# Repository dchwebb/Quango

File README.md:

# Quango

Quango
--------

Quango is a combined MIDI interface, VCA and envelope for controlling four voice polyphonic Eurorack Modular Oscillators. Polyphonic signal interconnections are made via RJ-45 cables (ie Ethernet cables).

Quango can control two VCOs simultaneously, supplying 1V/Octave pitch information and then shaping the returned audio using 8 ADSR envelopes controlling VCAs for each voice.

The MIDI interface receives both USB and serial MIDI data and also features a calibration mechanism where the pitch CV for each voice is adjusted to correct any tuning errors.

Each of the two channels uses an RJ-45 connector to send CV data on lines 1-4 and receive audio data on lines 5-8. The received audio data is used both for pitch calibration and sent into the ADSR-controlled VCAs.

Both channel voices are mixed and output onto an RJ-45 connection. Additionally each channel's four voices can be separately output on a header on the back of the unit. the gate signal for each voice is also output on an RJ-45 for controlling external envelopes etc.

Additional controls include an octave switch to allow channel B's CV range to be adjusted up or down an octave and a fader to control the overall level of each voice. LEDs show the current level of the VCA of each voice for each channel.

Technical
---------

Quango uses an STM32G473 microcontroller which handles the MIDI interfacing, generates 12-bit DAC signals to control the envelopes, reads the front panel controls from its internal ADCs and controls two external DACs for generating the pitch CV and one envelope (the microcontroller has 7 internal 12 bit DACs so the 8th envelope is supplied from an external 12 bit DAC).

The 1V/Octave Pitch output is generated using an SPI controlled 16-bit 8 channel Analog Devices AD5676 DAC. A Microchip MCP48 12 bit DAC outputs the one envelope generated externally to the microcontroller. Alfa AS3364 quad linear VCAs are used for independent level control of each channel.

A PS508 audio multiplexer switches the 8 audio input channels to a single ADC channel on the microcontroller for pitch detection. Output level LEDs are controlled via PWM from the microcontroller.

Construction is a sandwich of three PCBs with a component board, a controls board and a panel. PCBs designed in Kicad v6.

[Components schematic](https://raw.githubusercontent.com/dchwebb/Quango/master/Hardware/Quango_Components.pdf)

[Controls schematic](https://raw.githubusercontent.com/dchwebb/Quango/master/Hardware/Quango_Controls.pdf)

In addition the the Eurorack +/-12V rails (which have polarity protection and filtering) a 5v rail is supplied using an AMS1117-5.0 LDO. A 3.3v rail is generated with an LM1117-3.3.

Errata
------

Version 1 of the component PCB had the power supply connections to op-amp U14 reversed.

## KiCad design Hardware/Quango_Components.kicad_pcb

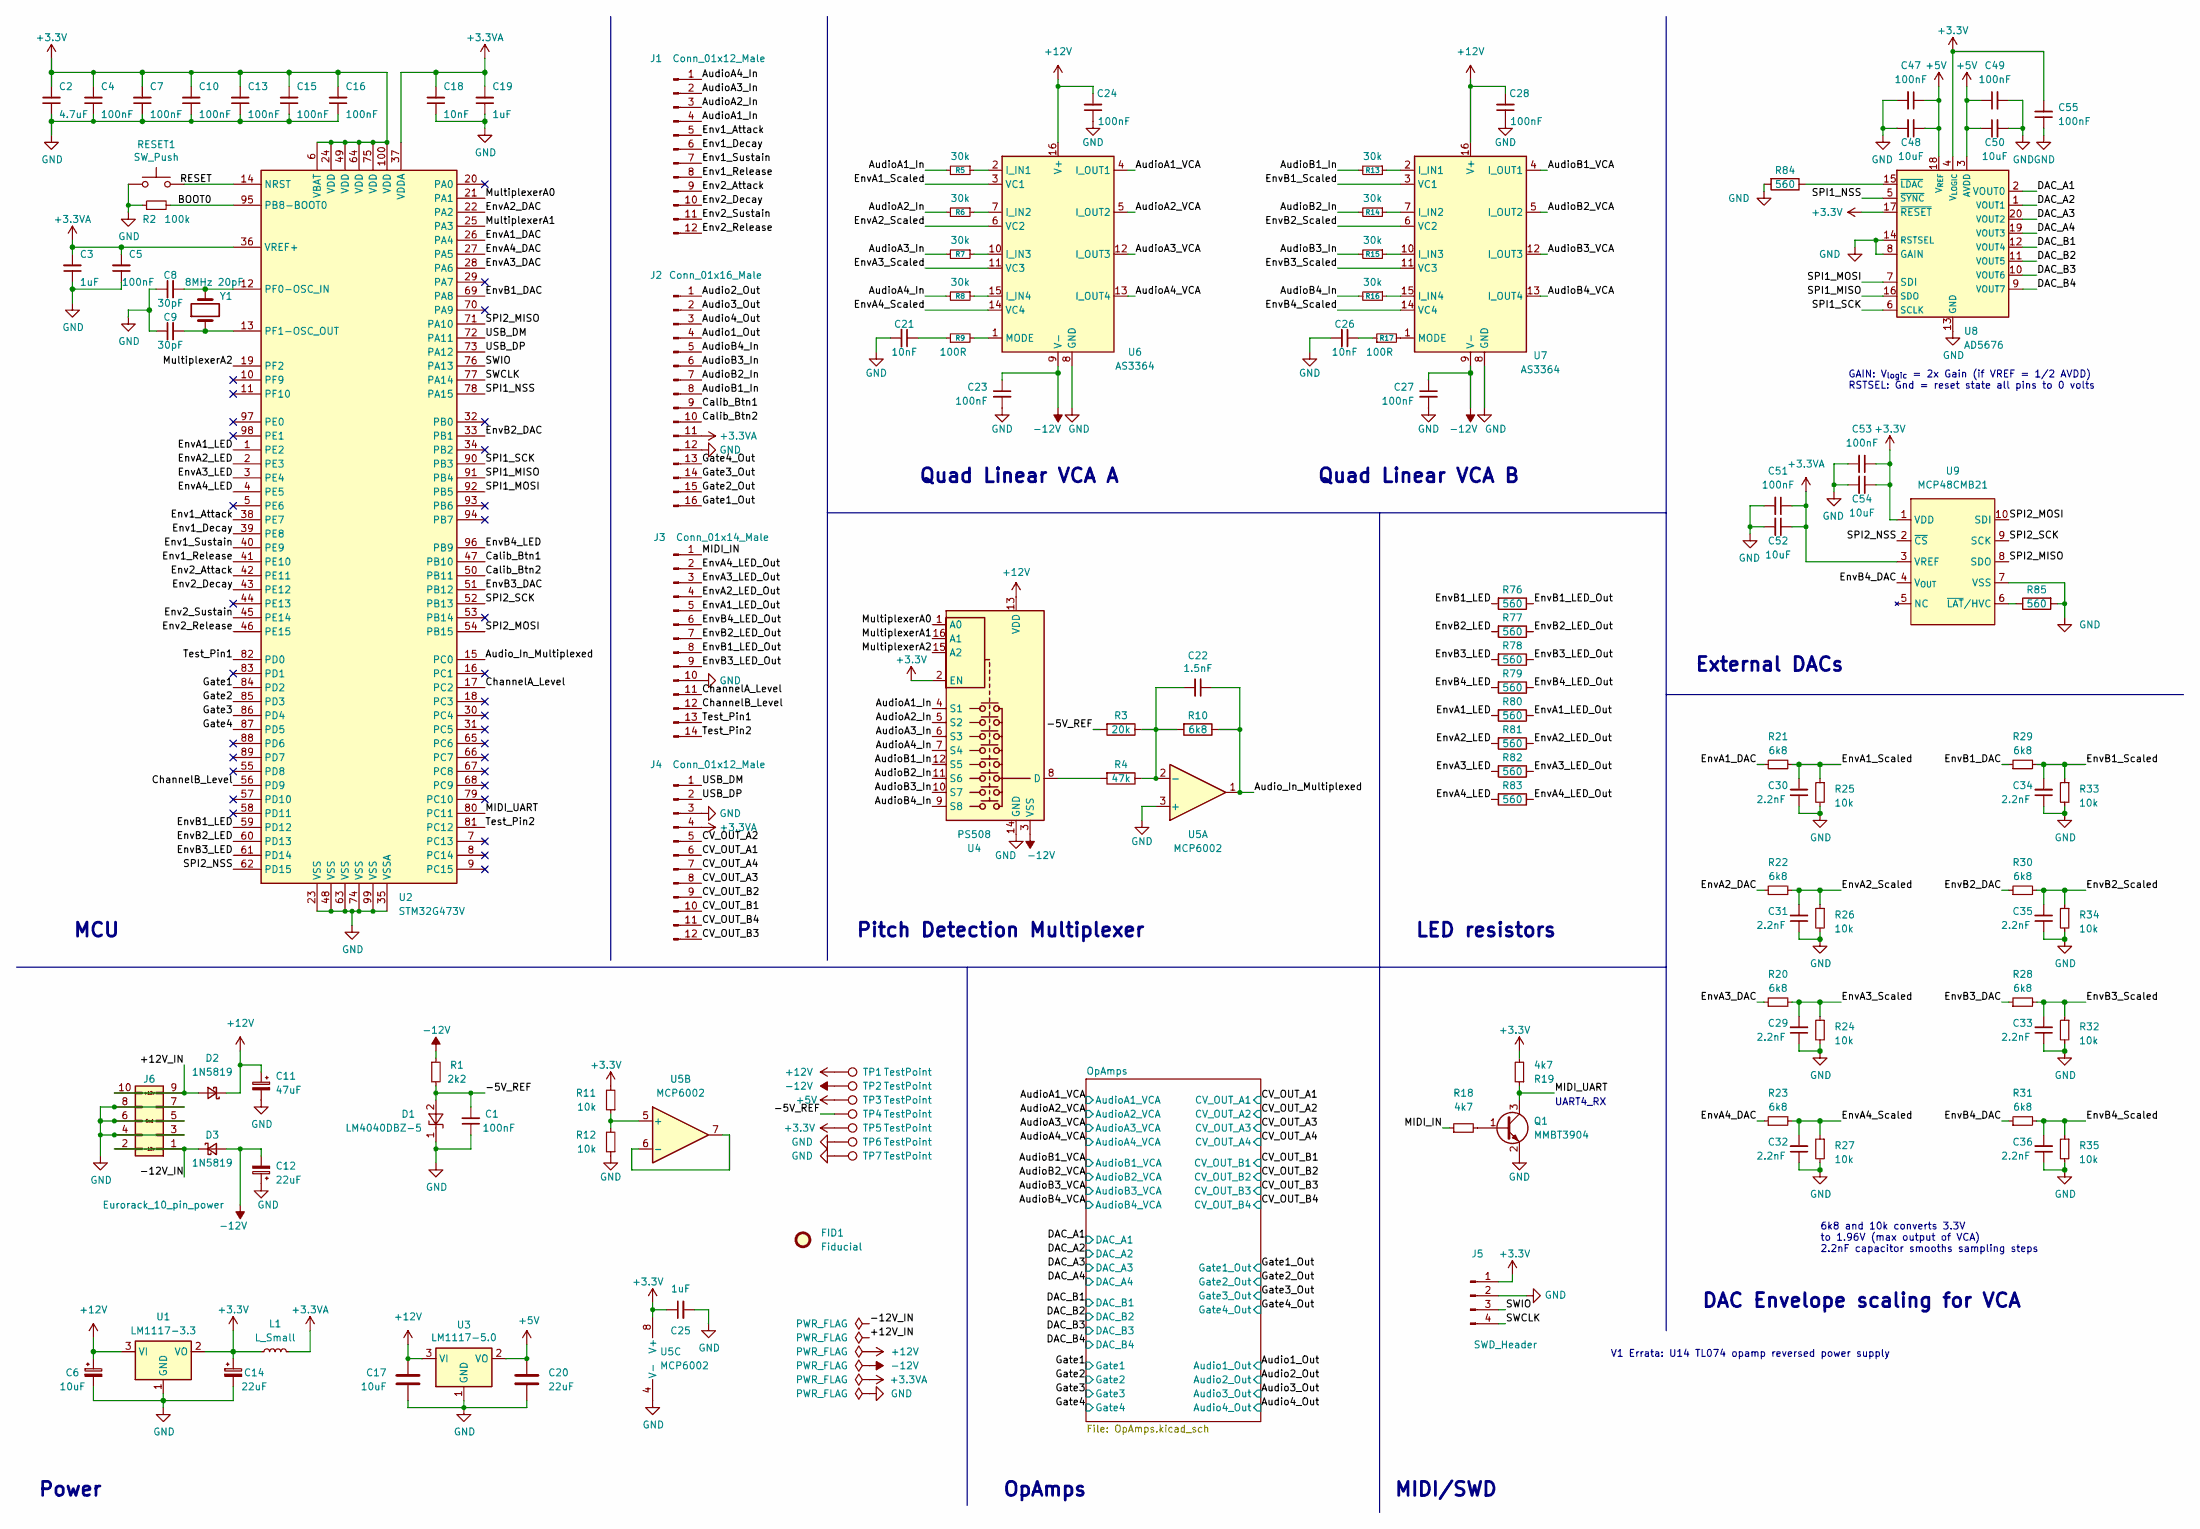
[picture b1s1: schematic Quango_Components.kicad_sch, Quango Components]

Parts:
C1, C4, C5, C7, C10, C13, C15, C16, C23, C24, C27, C28: 100nF; C_0603_1608Metric; Part_Number C14663
C2: 4.7uF; C_0603_1608Metric; Part_Number C19666
C3, C19: 1uF; C_0603_1608Metric; Part_Number C15849
C6, C17: 10uF; C_1206_3216Metric
C8, C9: 30pF; C_0603_1608Metric; Part_Number C22397
C11: 47uF; CP_Elec_4x5.8
C12, C14, C20: 22uF; CP_Elec_4x5.8
C18, C21, C26: 10nF; C_0603_1608Metric; Part_Number C57112
C22: 1.5nF; C_0603_1608Metric; Part_Number C1595
C25: 1uF; C_0603_1608Metric
C29, C30, C31, C32, C33, C34, C35, C36: 2.2nF; C_0603_1608Metric; Part_Number C1604
C47, C49, C51, C53, C55: 100nF; C_0603_1608Metric
C48, C50, C52, C54: 10uF; C_0805_2012Metric
D1: LM4040DBZ-5; SOT-23; Part_Number C156291
D2, D3: 1N5819; D_SOD-123
FID1: Fiducial; 4_Layer_Markers
J1, J4: Conn_01x12_Male; PinHeader_1x12_P2.54mm_Vertical
J2: Conn_01x16_Male; PinHeader_1x16_P2.54mm_Vertical
J3: Conn_01x14_Male; PinHeader_1x14_P2.54mm_Vertical
J5: SWD_Header; SWD_header
J6: Eurorack_10_pin_power; Eurorack_10_pin_header
L1: L_Small; L_0805_2012Metric_Pad1.05x1.20mm_HandSolder; Part_Number C1046
Q1: MMBT3904; SOT-23; Part_Number C20526
R1: 2k2; R_0603_1608Metric; Part_Number C4190
R2: 100k; R_0603_1608Metric; Part_Number C25803
R3: 20k; R_0603_1608Metric; Part_Number C4184
R4: 47k; R_0603_1608Metric; Part_Number C25819
R5, R6, R7, R8, R13, R14, R15, R16: 30k; R_0603_1608Metric; Part_Number C22984
R9, R17: 100R; R_0603_1608Metric; Part_Number C22775
R10, R20, R21, R22, R23, R28, R29, R30, R31: 6k8; R_0603_1608Metric; Part_Number C23212
R11, R12: 10k; R_0603_1608Metric; Part_Number C23162
R18, R19: 4k7; R_0603_1608Metric; Part_Number C23162
R24, R25, R26, R27, R32, R33, R34, R35: 10k; R_0603_1608Metric; Part_Number C25804
R76, R77, R78, R79, R80, R81, R82, R83, R84, R85: 560; R_0603_1608Metric; Part_Number C23212
RESET1: SW_Push; SW_SPST_EVQQ2
TP1, TP2, TP3, TP4, TP5, TP6, TP7: TestPoint; 1mm_Test_Point
U1: LM1117-3.3; SOT-223-3_TabPin2
U2: STM32G473V; LQFP-100_14x14mm_P0.5mm
U3: LM1117-5.0; SOT-223-3_TabPin2
U4: PS508; TSSOP-16_4.4x5mm_P0.65mm
U5: MCP6002; SOIC-8_3.9x4.9mm_P1.27mm
U6, U7: AS3364; SOIC-16_3.9x9.9mm_P1.27mm
U8: AD5676; TSSOP-20_4.4x6.5mm_P0.65mm
U9: MCP48CMB21; MSOP-10_3x3mm_P0.5mm
Y1: 8MHz 20pF; Crystal_SMD_0603-2Pin_6.0x3.5mm; Part_Number C115962

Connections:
+3.3V: C2.2, C4.2, C7.2, C10.2, C13.2, C14.1, C15.2, C16.2, C25.1, C53.1, C54.1, C55.2, J5.1, L1.1, R11.2, R19.2, TP5.1, U1.2 (VO), U2.6 (VBAT), U2.24 (VDD), U2.49 (VDD), U2.64 (VDD), U2.75 (VDD), U2.100 (VDD), U4.2 (EN), U5.8 (V+), U8.4 (V_{LOGIC}), U8.17 (~RESET), U9.1 (VDD)
+3.3VA: C3.2, C5.2, C18.2, C19.2, C51.1, C52.1, J2.11, J4.4, L1.2, U2.36 (VREF+), U2.37 (VDDA), U9.3 (VREF)
+5V: C20.1, C47.1, C48.1, C49.1, C50.1, TP3.1, U3.2 (VO), U8.3 (AVDD), U8.18 (V_{REF})
+12V: C6.1, C11.1, C17.1, C24.2, C28.2, D2.1 (K), TP1.1, U1.3 (VI), U3.3 (VI), U4.13 (VDD), U6.16 (V+), U7.16 (V+); also elsewhere on the board
-12V: C12.2, C23.1, C27.1, D3.2 (A), R1.1, TP2.1, U4.3 (VSS), U6.9 (V-), U7.9 (V-); also elsewhere on the board
/+12V_IN: D2.2 (A), J6.9, J6.10
/-5V_REF: C1.2, D1.2 (A), R1.2, R3.2, TP4.1
/-12V_IN: D3.1 (K), J6.1, J6.2
/Audio1_Out: J2.4; also elsewhere on the board
/Audio2_Out: J2.1; also elsewhere on the board
/Audio3_Out: J2.2; also elsewhere on the board
/Audio4_Out: J2.3; also elsewhere on the board
/AudioA1_In: J1.4, R5.2, U4.4 (S1)
/AudioA1_VCA: U6.4 (I_OUT1); also elsewhere on the board
/AudioA2_In: J1.3, R6.2, U4.5 (S2)
/AudioA2_VCA: U6.5 (I_OUT2); also elsewhere on the board
/AudioA3_In: J1.2, R7.2, U4.6 (S3)
/AudioA3_VCA: U6.12 (I_OUT3); also elsewhere on the board
/AudioA4_In: J1.1, R8.2, U4.7 (S4)
/AudioA4_VCA: U6.13 (I_OUT4); also elsewhere on the board
/AudioB1_In: J2.8, R13.2, U4.12 (S5)
/AudioB1_VCA: U7.4 (I_OUT1); also elsewhere on the board
/AudioB2_In: J2.7, R14.2, U4.11 (S6)
/AudioB2_VCA: U7.5 (I_OUT2); also elsewhere on the board
/AudioB3_In: J2.6, R15.2, U4.10 (S7)
/AudioB3_VCA: U7.12 (I_OUT3); also elsewhere on the board
/AudioB4_In: J2.5, R16.2, U4.9 (S8)
/AudioB4_VCA: U7.13 (I_OUT4); also elsewhere on the board
/Audio_In_Multiplexed: C22.1, R10.1, U2.15 (PC0), U5.1
/BOOT0: R2.2, U2.95 (PB8-BOOT0)
/CV_OUT_A1: J4.6; also elsewhere on the board
/CV_OUT_A2: J4.5; also elsewhere on the board
/CV_OUT_A3: J4.8; also elsewhere on the board
/CV_OUT_A4: J4.7; also elsewhere on the board
/CV_OUT_B1: J4.10; also elsewhere on the board
/CV_OUT_B2: J4.9; also elsewhere on the board
/CV_OUT_B3: J4.12; also elsewhere on the board
/CV_OUT_B4: J4.11; also elsewhere on the board
/Calib_Btn1: J2.9, U2.47 (PB10)
/Calib_Btn2: J2.10, U2.50 (PB11)
/ChannelA_Level: J3.11, U2.17 (PC2)
/ChannelB_Level: J3.12, U2.56 (PD9)
/DAC_A1: U8.2 (VOUT0); also elsewhere on the board
/DAC_A2: U8.1 (VOUT1); also elsewhere on the board
/DAC_A3: U8.20 (VOUT2); also elsewhere on the board
/DAC_A4: U8.19 (VOUT3); also elsewhere on the board
/DAC_B1: U8.12 (VOUT4); also elsewhere on the board
/DAC_B2: U8.11 (VOUT5); also elsewhere on the board
/DAC_B3: U8.10 (VOUT6); also elsewhere on the board
/DAC_B4: U8.9 (VOUT7); also elsewhere on the board
/Env1_Attack: J1.5, U2.38 (PE7)
/Env1_Decay: J1.6, U2.39 (PE8)
/Env1_Release: J1.8, U2.41 (PE10)
/Env1_Sustain: J1.7, U2.40 (PE9)
/Env2_Attack: J1.9, U2.42 (PE11)
/Env2_Decay: J1.10, U2.43 (PE12)
/Env2_Release: J1.12, U2.46 (PE15)
/Env2_Sustain: J1.11, U2.45 (PE14)
/EnvA1_DAC: R21.1, U2.26 (PA4)
/EnvA1_LED: R80.2, U2.1 (PE2)
/EnvA1_LED_Out: J3.5, R80.1
/EnvA1_Scaled: C30.2, R21.2, R25.1, U6.3 (VC1)
/EnvA2_DAC: R22.1, U2.22 (PA2)
/EnvA2_LED: R81.2, U2.2 (PE3)
/EnvA2_LED_Out: J3.4, R81.1
/EnvA2_Scaled: C31.2, R22.2, R26.1, U6.6 (VC2)
/EnvA3_DAC: R20.1, U2.28 (PA6)
/EnvA3_LED: R82.2, U2.3 (PE4)
/EnvA3_LED_Out: J3.3, R82.1
/EnvA3_Scaled: C29.2, R20.2, R24.1, U6.11 (VC3)
/EnvA4_DAC: R23.1, U2.27 (PA5)
/EnvA4_LED: R83.2, U2.4 (PE5)
/EnvA4_LED_Out: J3.2, R83.1
/EnvA4_Scaled: C32.2, R23.2, R27.1, U6.14 (VC4)
/EnvB1_DAC: R29.1, U2.69 (PA8)
/EnvB1_LED: R76.2, U2.59 (PD12)
/EnvB1_LED_Out: J3.8, R76.1
/EnvB1_Scaled: C34.2, R29.2, R33.1, U7.3 (VC1)
/EnvB2_DAC: R30.1, U2.33 (PB1)
/EnvB2_LED: R77.2, U2.60 (PD13)
/EnvB2_LED_Out: J3.7, R77.1
/EnvB2_Scaled: C35.2, R30.2, R34.1, U7.6 (VC2)
/EnvB3_DAC: R28.1, U2.51 (PB12)
/EnvB3_LED: R78.2, U2.61 (PD14)
/EnvB3_LED_Out: J3.9, R78.1
/EnvB3_Scaled: C33.2, R28.2, R32.1, U7.11 (VC3)
/EnvB4_DAC: R31.1, U9.4 (V_{OUT})
/EnvB4_LED: R79.2, U2.96 (PB9)
/EnvB4_LED_Out: J3.6, R79.1
/EnvB4_Scaled: C36.2, R31.2, R35.1, U7.14 (VC4)
/Gate1: U2.84 (PD2); also elsewhere on the board
/Gate1_Out: J2.16; also elsewhere on the board
/Gate2: U2.85 (PD3); also elsewhere on the board
/Gate2_Out: J2.15; also elsewhere on the board
/Gate3: U2.86 (PD4); also elsewhere on the board
/Gate3_Out: J2.14; also elsewhere on the board
/Gate4: U2.87 (PD5); also elsewhere on the board
/Gate4_Out: J2.13; also elsewhere on the board
/MIDI_IN: J3.1, R18.1
/MIDI_UART: Q1.3 (C), R19.1, U2.80 (PC11)
/MultiplexerA0: U2.21 (PA1), U4.1 (A0)
/MultiplexerA1: U2.25 (PA3), U4.16 (A1)
/MultiplexerA2: U2.19 (PF2), U4.15 (A2)
/RESET: RESET1.1, U2.14 (NRST)
/SPI1_MISO: U2.91 (PB4), U8.16 (SDO)
/SPI1_MOSI: U2.92 (PB5), U8.7 (SDI)
/SPI1_NSS: U2.78 (PA15), U8.5 (~SYNC)
/SPI1_SCK: U2.90 (PB3), U8.6 (SCLK)
/SPI2_MISO: U2.71 (PA10), U9.8 (SDO)
/SPI2_MOSI: U2.54 (PB15), U9.10 (SDI)
/SPI2_NSS: U2.62 (PD15), U9.2 (~CS)
/SPI2_SCK: U2.52 (PB13), U9.9 (SCK)
/SWCLK: J5.4, U2.77 (PA14)
/SWIO: J5.3, U2.76 (PA13)
/Test_Pin1: J3.13, U2.82 (PD0)
/Test_Pin2: J3.14, U2.81 (PC12)
/USB_DM: J4.1, U2.72 (PA11)
/USB_DP: J4.2, U2.73 (PA12)
GND: C1.1, C2.1, C3.1, C4.1, C5.1, C6.2, C7.1, C8.1, C9.1, C10.1, C11.2, C12.1, C13.1, C14.2, C15.1, C16.1, C17.2, C18.1, C19.1, C20.2, C21.2, C23.2, C24.1, C25.2, C26.2, C27.2, C28.1, C29.1, C30.1, C31.1, C32.1, C33.1, C34.1, C35.1, C36.1, C47.2, C48.2, C49.2, C50.2, C51.2, C52.2, C53.2, C54.2, C55.1, D1.1 (K), J2.12, J3.10, J4.3, J5.2, J6.3, J6.4, J6.5, J6.6, J6.7, J6.8, Q1.2 (E), R2.1, R12.1, R24.2, R25.2, R26.2, R27.2, R32.2, R33.2, R34.2, R35.2, R84.2, R85.2, RESET1.2, TP6.1, TP7.1, U1.1 (GND), U2.23 (VSS), U2.35 (VSSA), U2.48 (VSS), U2.63 (VSS), U2.74 (VSS), U2.99 (VSS), U3.1 (GND), U4.14 (GND), U5.3 (+), U5.4 (V-), U6.8 (GND), U7.8 (GND), U8.8 (GAIN), U8.13 (GND), U8.14 (RSTSEL), U9.7 (VSS); also elsewhere on the board
unnamed: C21.1, R9.1
unnamed: C26.1, R17.1
unnamed: Q1.1 (B), R18.2
unnamed: C8.2, U2.12 (PF0-OSC_IN), Y1.2
unnamed: C9.2, U2.13 (PF1-OSC_OUT), Y1.1
unnamed: R4.2, U4.8 (D)
unnamed: C22.2, R3.1, R4.1, R10.2, U5.2 (-)
unnamed: R11.1, R12.2, U5.5 (+)
unnamed: U5.6 (-), U5.7
unnamed: R5.1, U6.2 (I_IN1)
unnamed: R6.1, U6.7 (I_IN2)
unnamed: R7.1, U6.10 (I_IN3)
unnamed: R8.1, U6.15 (I_IN4)
unnamed: R9.2, U6.1 (MODE)
unnamed: R13.1, U7.2 (I_IN1)
unnamed: R14.1, U7.7 (I_IN2)
unnamed: R15.1, U7.10 (I_IN3)
unnamed: R16.1, U7.15 (I_IN4)
unnamed: R17.2, U7.1 (MODE)
unnamed: R84.1, U8.15 (~LDAC)
unnamed: R85.1, U9.6 (~LAT/HVC)

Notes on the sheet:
Pitch Detection Multiplexer
DAC Envelope scaling for VCA
Power
V1 Errata: U14 TL074 opamp reversed power supply
MCU
UART4_RX
GAIN: V_{logic} = 2x Gain (if VREF = 1/2 AVDD) RSTSEL: Gnd = reset state all pins to 0 volts
6k8 and 10k converts 3.3V to 1.96V (max output of VCA) 2.2nF capacitor smooths sampling steps
LED resistors
OpAmps
External DACs
Quad Linear VCA B
MIDI/SWD
Quad Linear VCA A

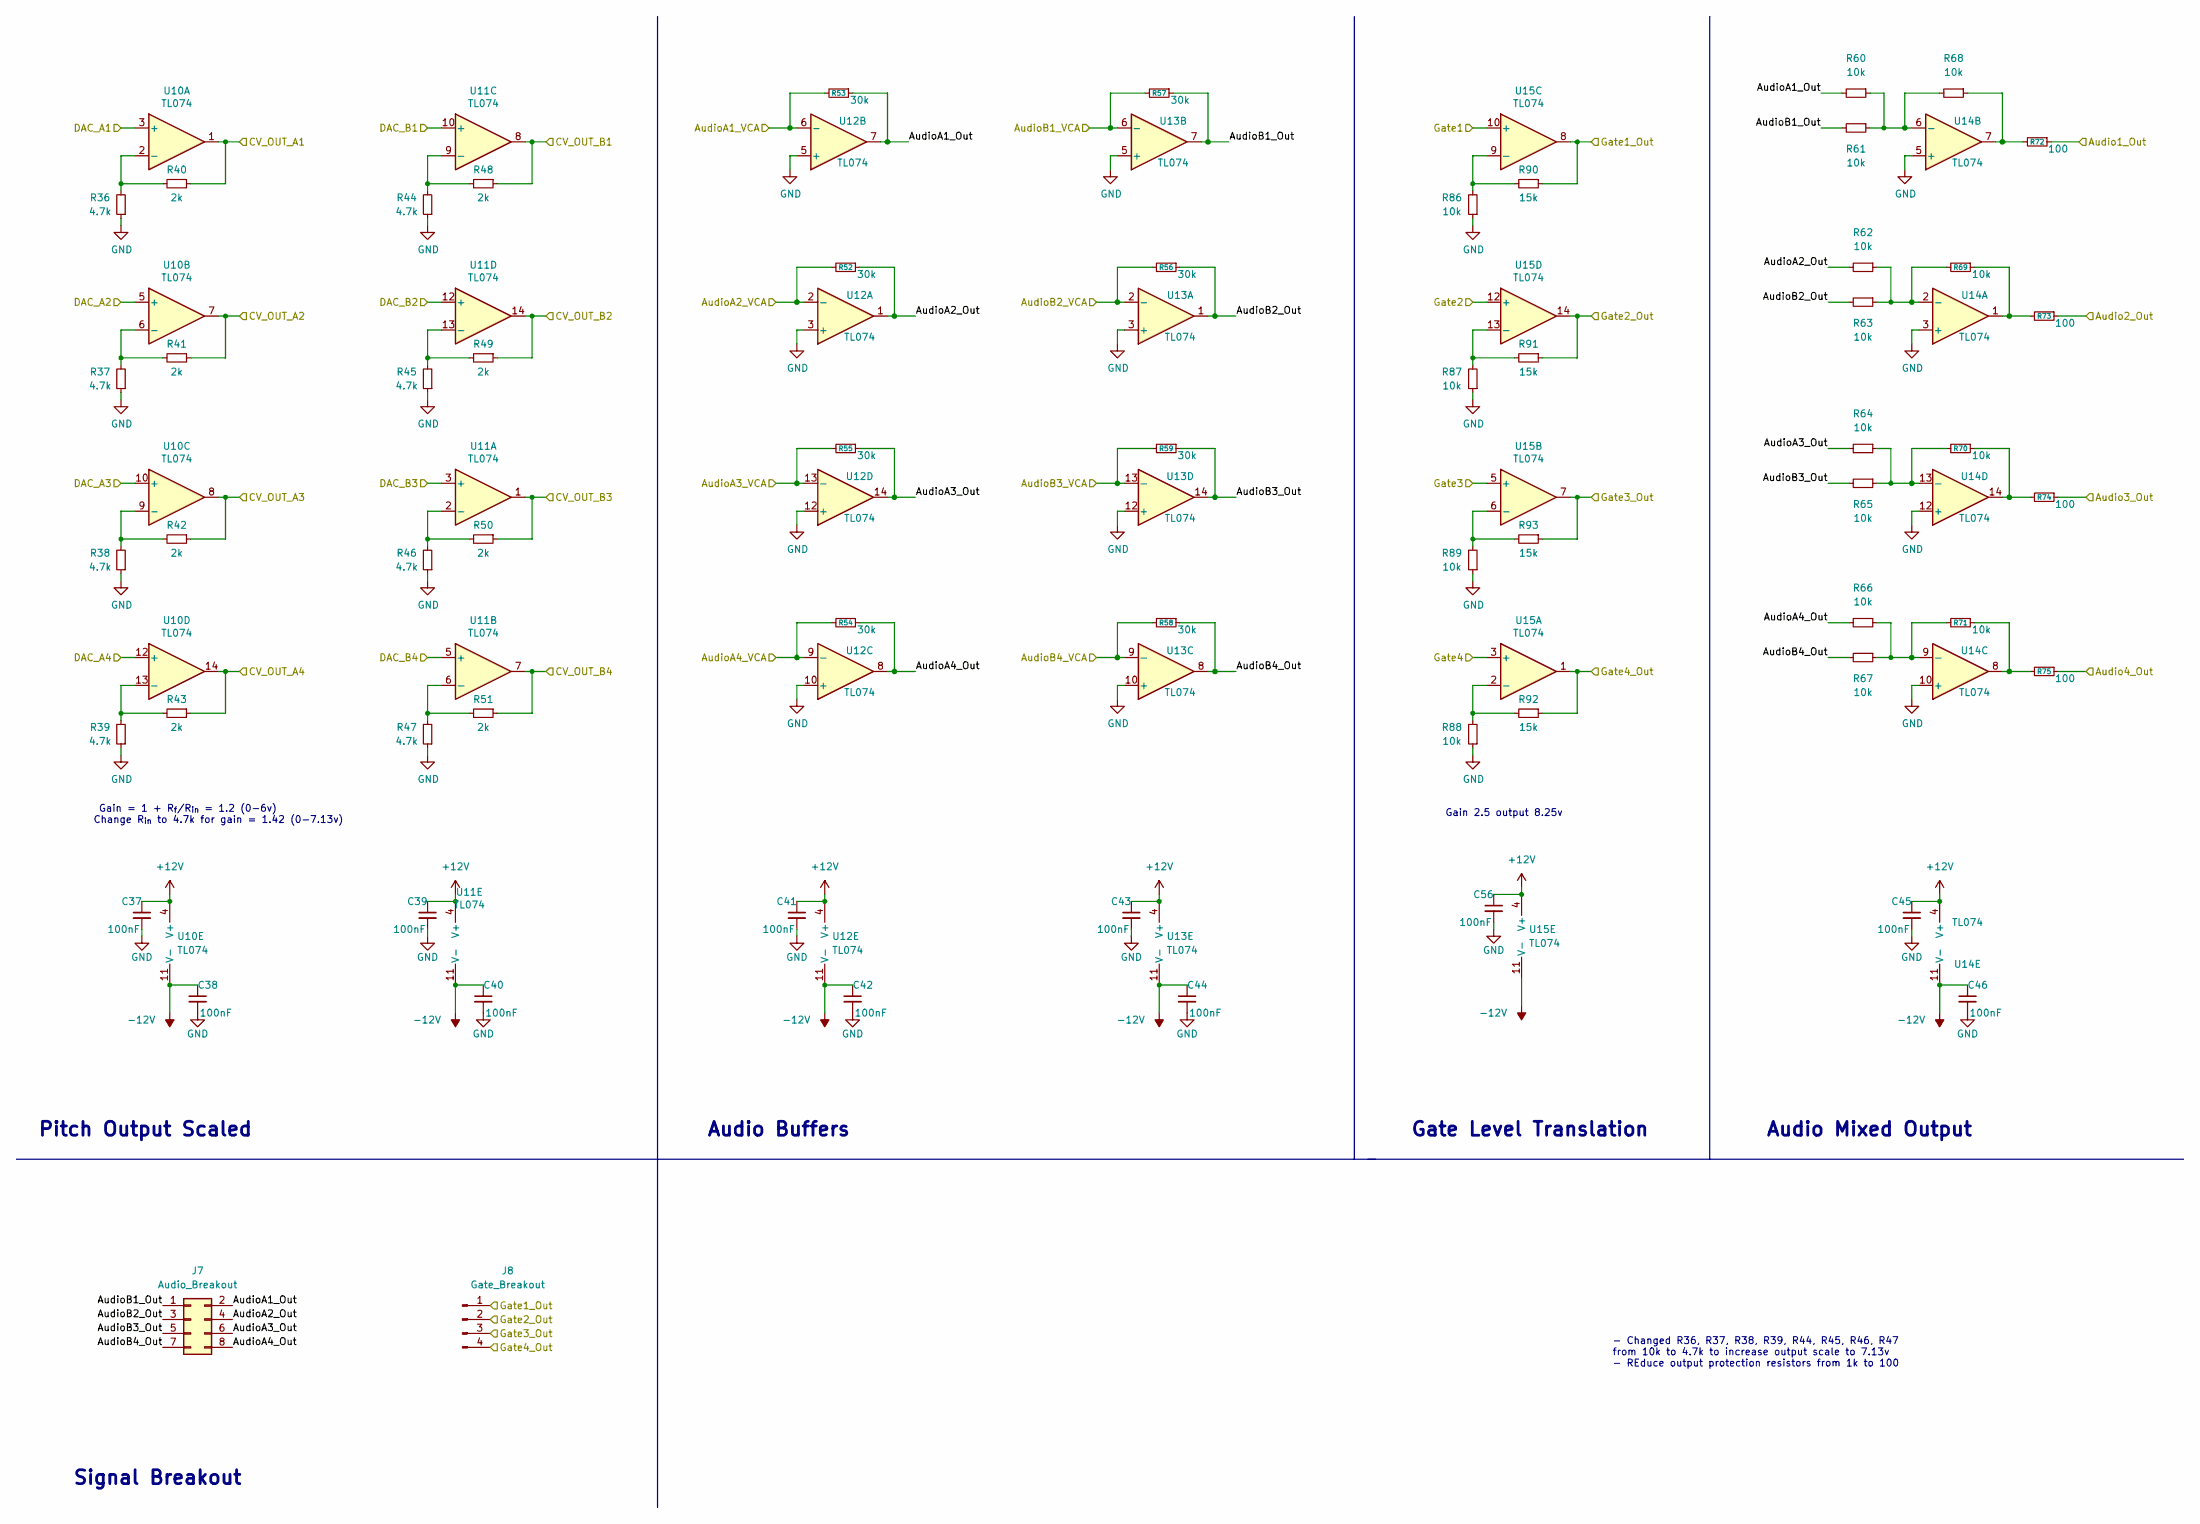
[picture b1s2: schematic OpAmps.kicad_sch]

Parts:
C37, C38, C39, C40, C41, C42, C43, C44, C45, C46, C56: 100nF; C_0603_1608Metric; Part_Number C23630
J7: Audio_Breakout; PinHeader_2x04_P2.54mm_Vertical
J8: Gate_Breakout; PinHeader_1x04_P2.54mm_Vertical
R36, R37, R38, R39, R44, R45, R46, R47: 4.7k; R_0603_1608Metric
R40, R41, R42, R43, R48, R49, R50, R51: 2k; R_0603_1608Metric
R52, R53, R54, R55, R56, R57, R58, R59: 30k; R_0603_1608Metric; Part_Number C22984
R60, R61, R62, R63, R64, R65, R66, R67, R68, R69, R70, R71: 10k; R_0603_1608Metric; Part_Number C22984
R72, R73, R74, R75: 100; R_0603_1608Metric; Part_Number C21190
R86, R87, R88, R89: 10k; R_0603_1608Metric
R90, R91, R92, R93: 15k; R_0603_1608Metric
U10, U11, U12, U13, U14, U15: TL074; TSSOP-14_4.4x5mm_P0.65mm

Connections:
+12V: C37.1, C39.1, C41.1, C43.1, C45.1, C56.1, U10.4 (V+), U11.4 (V+), U12.4 (V+), U13.4 (V+), U14.4 (V+), U15.4 (V+); also elsewhere on the board
-12V: C38.1, C40.1, C42.1, C44.1, C46.1, U10.11 (V-), U11.11 (V-), U12.11 (V-), U13.11 (V-), U14.11 (V-), U15.11 (V-); also elsewhere on the board
/Audio1_Out: R72.1; also elsewhere on the board
/Audio2_Out: R73.1; also elsewhere on the board
/Audio3_Out: R74.1; also elsewhere on the board
/Audio4_Out: R75.1; also elsewhere on the board
/AudioA1_VCA: R53.2, U12.6 (-); also elsewhere on the board
/AudioA2_VCA: R52.2, U12.2 (-); also elsewhere on the board
/AudioA3_VCA: R55.2, U12.13 (-); also elsewhere on the board
/AudioA4_VCA: R54.2, U12.9 (-); also elsewhere on the board
/AudioB1_VCA: R57.2, U13.6 (-); also elsewhere on the board
/AudioB2_VCA: R56.2, U13.2 (-); also elsewhere on the board
/AudioB3_VCA: R59.2, U13.13 (-); also elsewhere on the board
/AudioB4_VCA: R58.2, U13.9 (-); also elsewhere on the board
/CV_OUT_A1: R40.1, U10.1; also elsewhere on the board
/CV_OUT_A2: R41.1, U10.7; also elsewhere on the board
/CV_OUT_A3: R42.1, U10.8; also elsewhere on the board
/CV_OUT_A4: R43.1, U10.14; also elsewhere on the board
/CV_OUT_B1: R48.1, U11.8; also elsewhere on the board
/CV_OUT_B2: R49.1, U11.14; also elsewhere on the board
/CV_OUT_B3: R50.1, U11.1; also elsewhere on the board
/CV_OUT_B4: R51.1, U11.7; also elsewhere on the board
/DAC_A1: U10.3 (+); also elsewhere on the board
/DAC_A2: U10.5 (+); also elsewhere on the board
/DAC_A3: U10.10 (+); also elsewhere on the board
/DAC_A4: U10.12 (+); also elsewhere on the board
/DAC_B1: U11.10 (+); also elsewhere on the board
/DAC_B2: U11.12 (+); also elsewhere on the board
/DAC_B3: U11.3 (+); also elsewhere on the board
/DAC_B4: U11.5 (+); also elsewhere on the board
/Gate1: U15.10 (+); also elsewhere on the board
/Gate1_Out: J8.1, R90.1, U15.8; also elsewhere on the board
/Gate2: U15.12 (+); also elsewhere on the board
/Gate2_Out: J8.2, R91.1, U15.14; also elsewhere on the board
/Gate3: U15.5 (+); also elsewhere on the board
/Gate3_Out: J8.3, R93.1, U15.7; also elsewhere on the board
/Gate4: U15.3 (+); also elsewhere on the board
/Gate4_Out: J8.4, R92.1, U15.1; also elsewhere on the board
/OpAmps/AudioA1_Out: J7.2, R53.1, R60.2, U12.7
/OpAmps/AudioA2_Out: J7.4, R52.1, R62.2, U12.1
/OpAmps/AudioA3_Out: J7.6, R55.1, R64.2, U12.14
/OpAmps/AudioA4_Out: J7.8, R54.1, R66.2, U12.8
/OpAmps/AudioB1_Out: J7.1, R57.1, R61.2, U13.7
/OpAmps/AudioB2_Out: J7.3, R56.1, R63.2, U13.1
/OpAmps/AudioB3_Out: J7.5, R59.1, R65.2, U13.14
/OpAmps/AudioB4_Out: J7.7, R58.1, R67.2, U13.8
GND: C37.2, C38.2, C39.2, C40.2, C41.2, C42.2, C43.2, C44.2, C45.2, C46.2, C56.2, R36.1, R37.1, R38.1, R39.1, R44.1, R45.1, R46.1, R47.1, R86.1, R87.1, R88.1, R89.1, U12.3 (+), U12.5 (+), U12.10 (+), U12.12 (+), U13.3 (+), U13.5 (+), U13.10 (+), U13.12 (+), U14.3 (+), U14.5 (+), U14.10 (+), U14.12 (+); also elsewhere on the board
unnamed: R68.1, R72.2, U14.7
unnamed: R69.1, R73.2, U14.1
unnamed: R70.1, R74.2, U14.14
unnamed: R71.1, R75.2, U14.8
unnamed: R36.2, R40.2, U10.2 (-)
unnamed: R37.2, R41.2, U10.6 (-)
unnamed: R38.2, R42.2, U10.9 (-)
unnamed: R39.2, R43.2, U10.13 (-)
unnamed: R46.2, R50.2, U11.2 (-)
unnamed: R47.2, R51.2, U11.6 (-)
unnamed: R44.2, R48.2, U11.9 (-)
unnamed: R45.2, R49.2, U11.13 (-)
unnamed: R62.1, R63.1, R69.2, U14.2 (-)
unnamed: R60.1, R61.1, R68.2, U14.6 (-)
unnamed: R66.1, R67.1, R71.2, U14.9 (-)
unnamed: R64.1, R65.1, R70.2, U14.13 (-)
unnamed: R88.2, R92.2, U15.2 (-)
unnamed: R89.2, R93.2, U15.6 (-)
unnamed: R86.2, R90.2, U15.9 (-)
unnamed: R87.2, R91.2, U15.13 (-)

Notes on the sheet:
Signal Breakout
Gate Level Translation
Audio Buffers
Pitch Output Scaled
Audio Mixed Output
Gain 2.5 output 8.25v
Gain = 1 + R_{f}/R_{in} = 1.2 (0-6v) Change R_{in} to 4.7k for gain = 1.42 (0-7.13v)
- Changed R36, R37, R38, R39, R44, R45, R46, R47 from 10k to 4.7k to increase output scale to 7.13v - REduce output protection resistors from 1k to 100

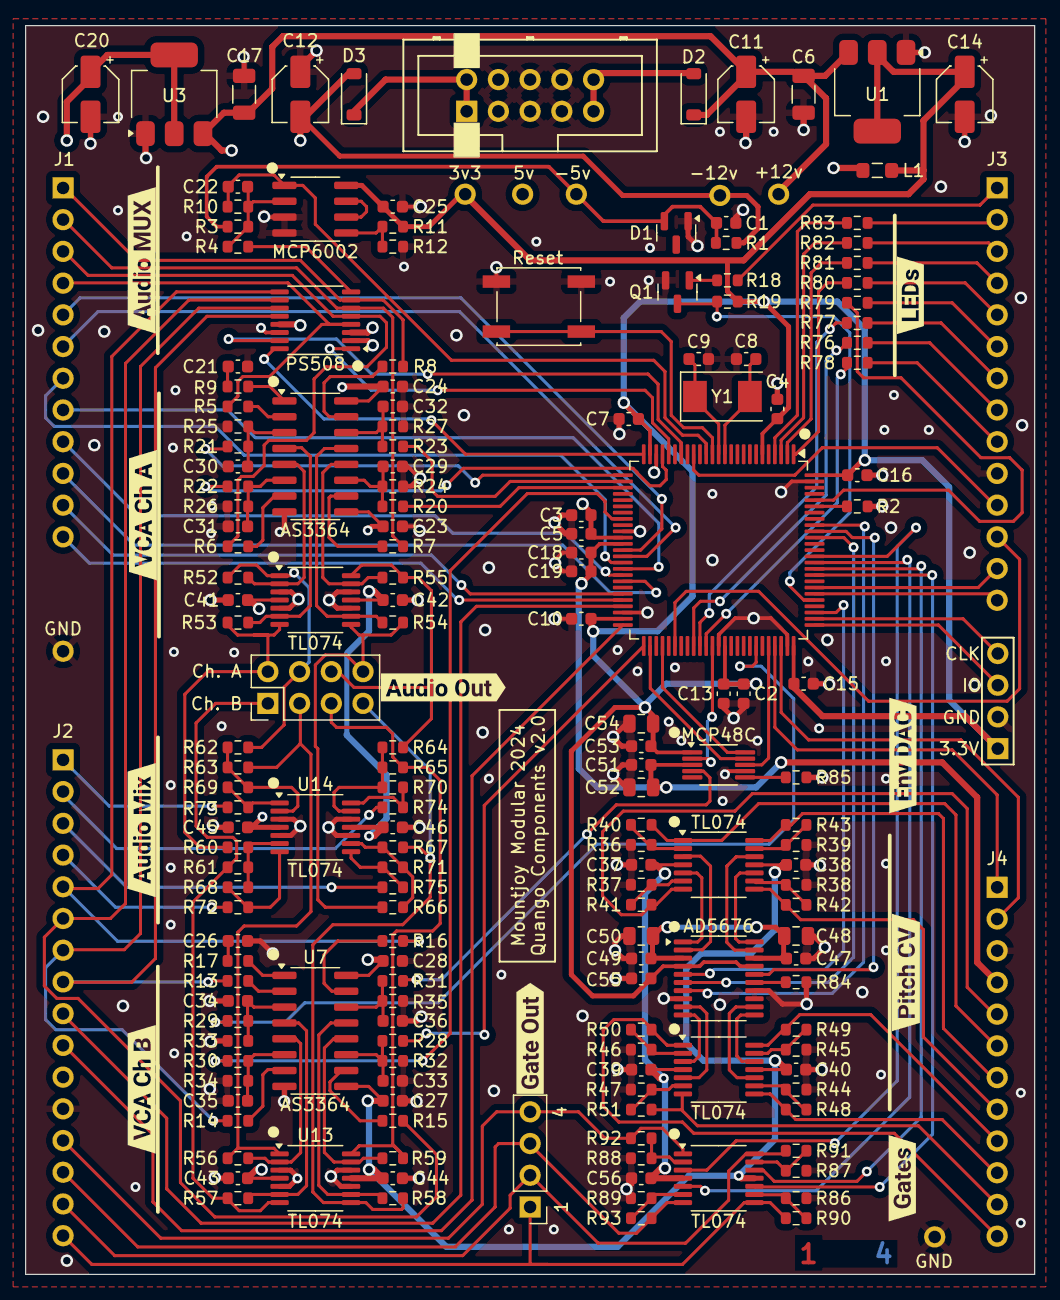
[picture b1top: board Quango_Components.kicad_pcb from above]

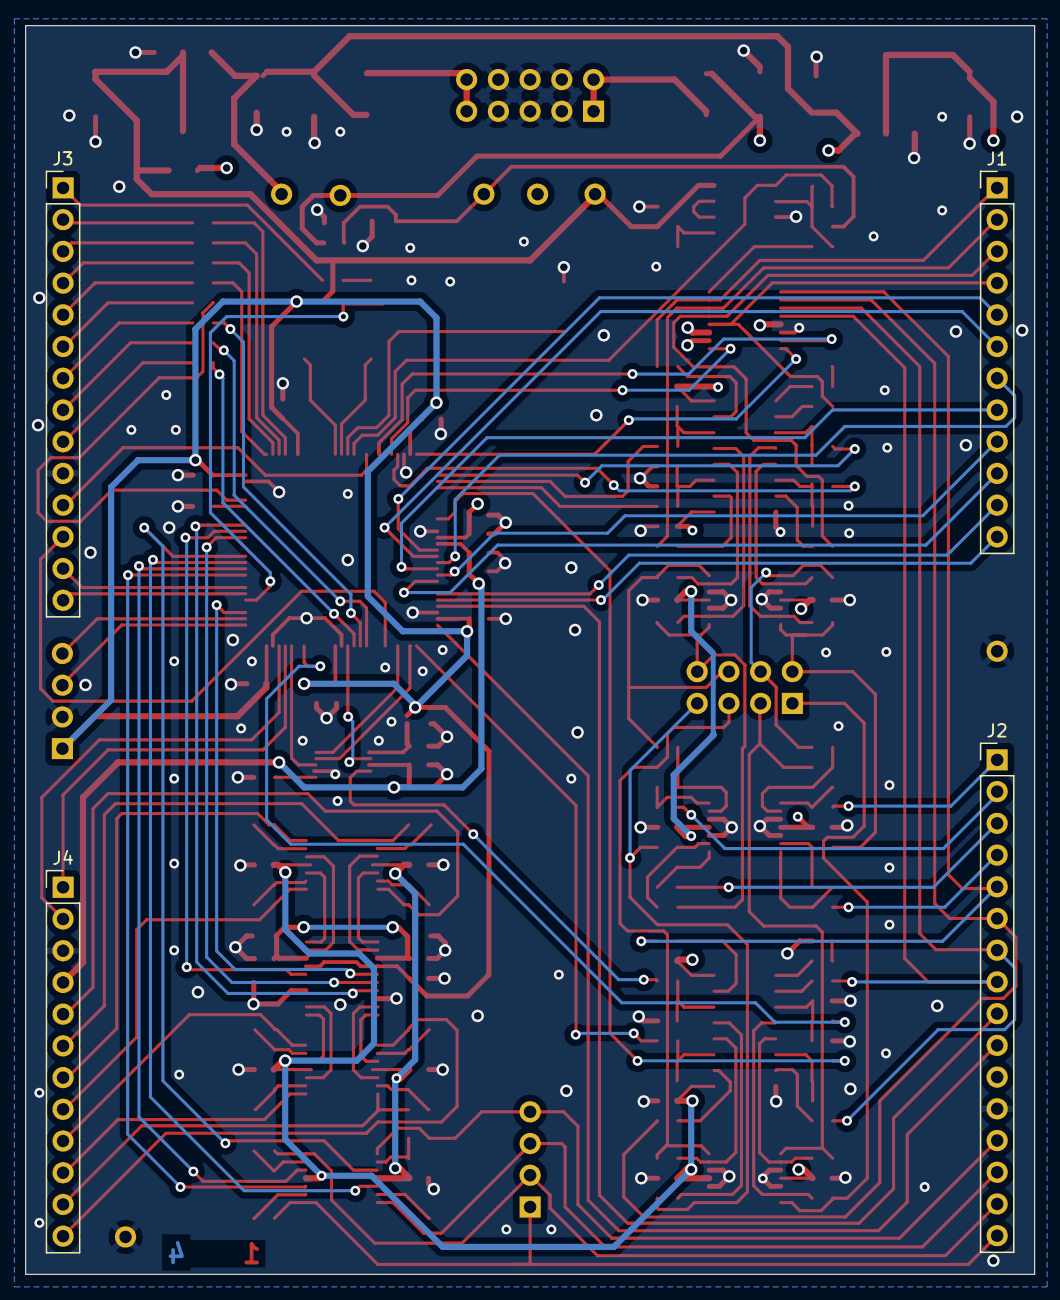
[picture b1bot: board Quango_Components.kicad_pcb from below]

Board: 4 copper layers, 80.8 x 100.0 mm, 197 parts (4 on the bottom side), 168 nets.

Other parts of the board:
kibuzzard-646A06F2: G***; kibuzzard-646A06F2
kibuzzard-646A061F: G***; kibuzzard-646A061F
kibuzzard-646A076E: G***; kibuzzard-646A076E
kibuzzard-646A0602: G***; kibuzzard-646A0602
kibuzzard-646B91AE: G***; kibuzzard-646B91AE
kibuzzard-646B91BF: G***; kibuzzard-646B91BF
kibuzzard-646B918A: G***; kibuzzard-646B918A
kibuzzard-646B919C: G***; kibuzzard-646B919C
kibuzzard-646B935C: G***; kibuzzard-646B935C
kibuzzard-646B9368: G***; kibuzzard-646B9368

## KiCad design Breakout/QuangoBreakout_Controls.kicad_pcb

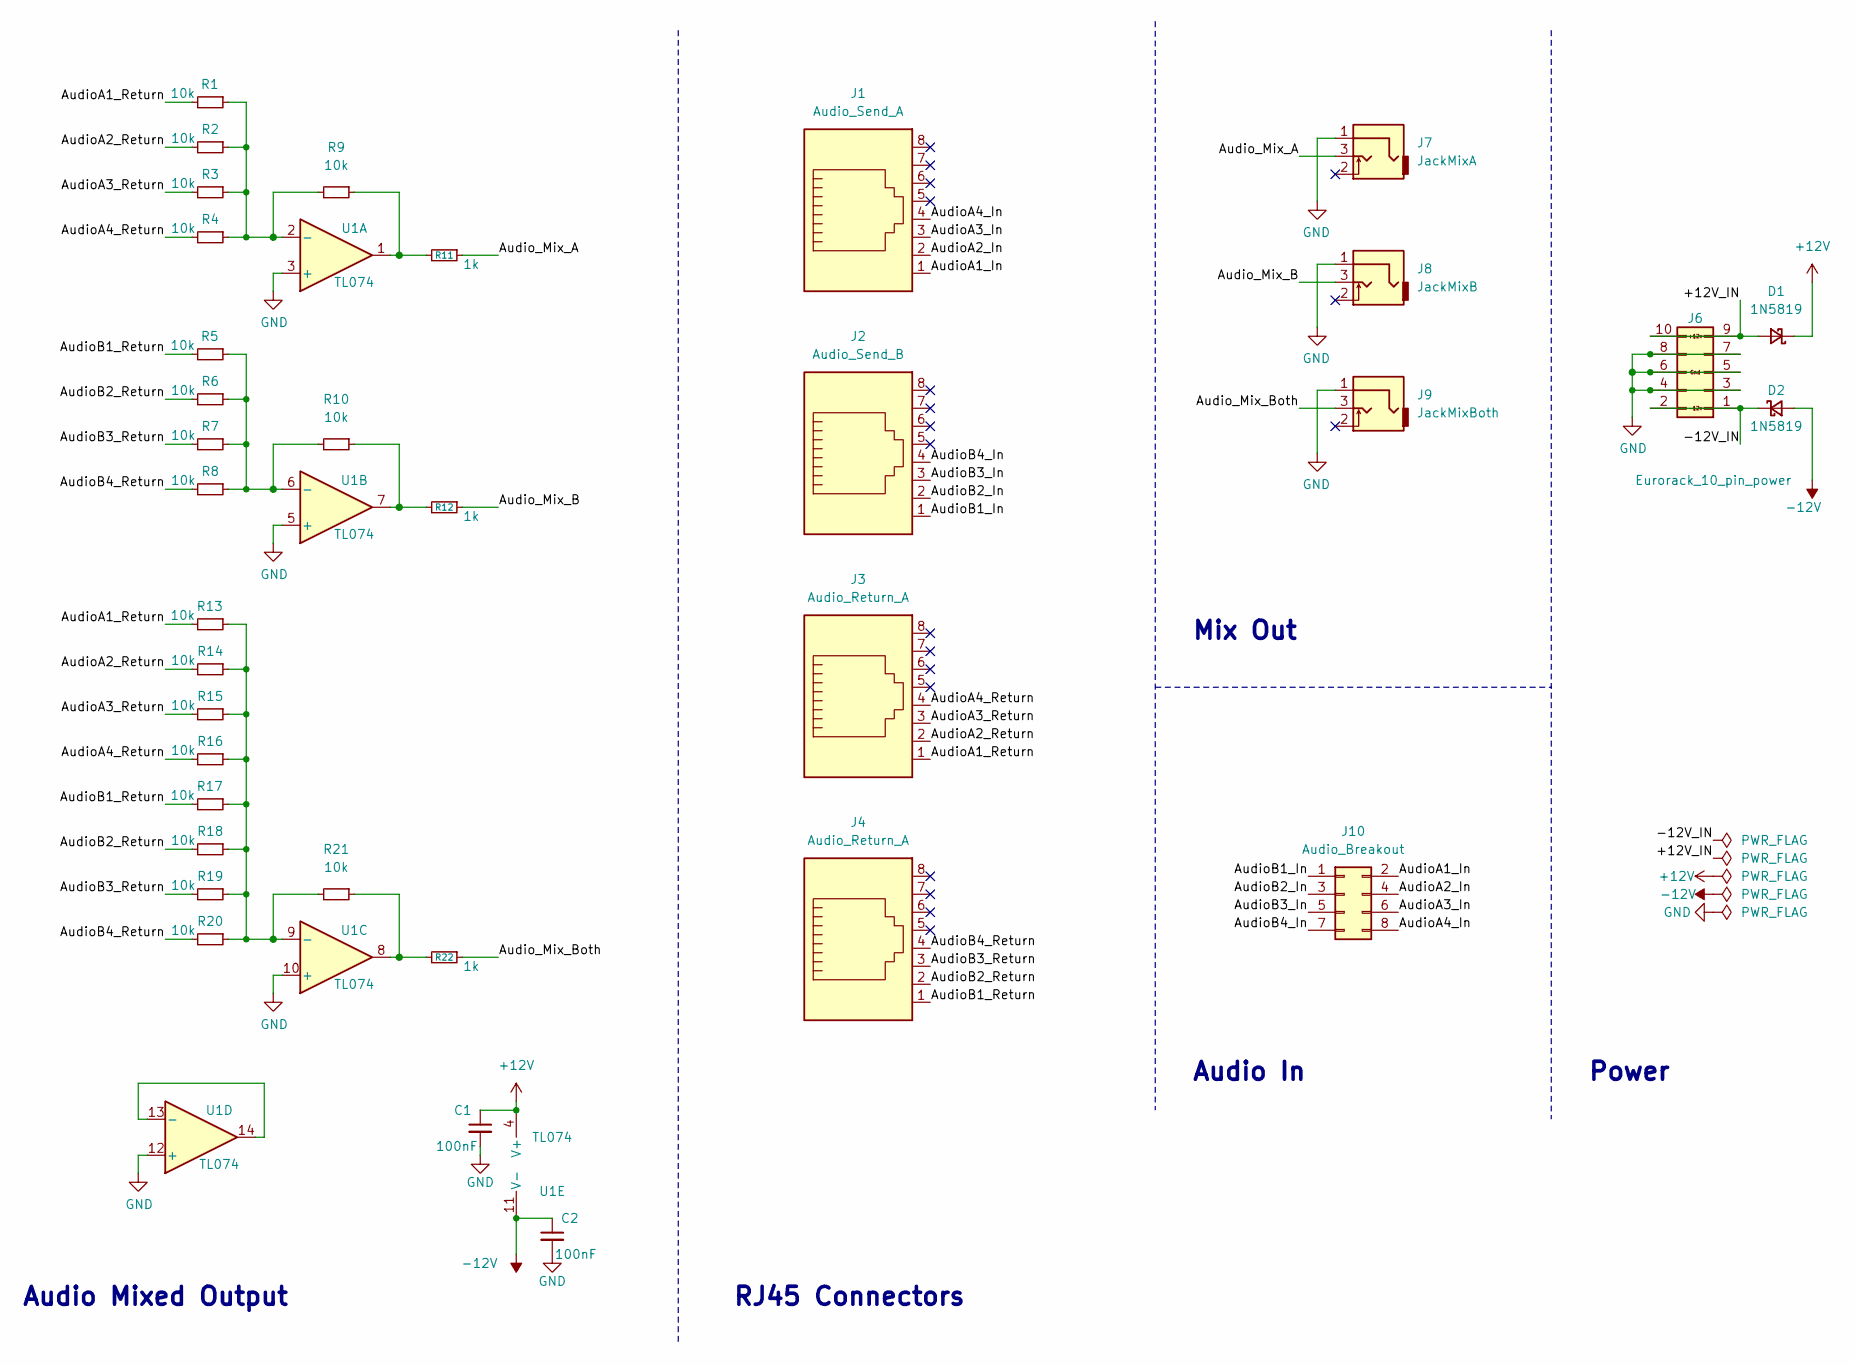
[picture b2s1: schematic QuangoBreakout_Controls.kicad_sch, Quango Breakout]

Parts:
C1, C2: 100nF; C_0603_1608Metric; Part_Number C23630
D1, D2: 1N5819; D_SOD-123
J1: Audio_Send_A; RJ45_Amphenol_RJHSE-3080
J2: Audio_Send_B; RJ45_Amphenol_RJHSE-3080
J3, J4: Audio_Return_A; RJ45_Amphenol_RJHSE-3080
J6: Eurorack_10_pin_power; PinHeader_2x05_P2.54mm_Vertical
J7: JackMixA; THONKICONN_hole
J8: JackMixB; THONKICONN_hole
J9: JackMixBoth; THONKICONN_hole
J10: Audio_Breakout; PinHeader_2x04_P2.54mm_Vertical
R1, R2, R3, R4, R5, R6, R7, R8, R9, R10, R13, R14, R15, R16, R17, R18, R19, R20, R21: 10k; R_0603_1608Metric; Part_Number C22984
R11, R12, R22: 1k; R_0603_1608Metric; Part_Number C21190
U1: TL074; SOIC-14_3.9x8.7mm_P1.27mm

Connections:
+12V: C1.1, D1.1 (K), U1.4 (V+)
-12V: C2.1, D2.2 (A), U1.11 (V-)
/+12V_IN: D1.2 (A), J6.9, J6.10
/-12V_IN: D2.1 (K), J6.1, J6.2
/AudioA1_In: J1.1, J10.2
/AudioA1_Return: J3.1, R1.2, R13.2
/AudioA2_In: J1.2, J10.4
/AudioA2_Return: J3.2, R2.2, R14.2
/AudioA3_In: J1.3, J10.6
/AudioA3_Return: J3.3, R3.2, R15.2
/AudioA4_In: J1.4, J10.8
/AudioA4_Return: J3.4, R4.2, R16.2
/AudioB1_In: J2.1, J10.1
/AudioB1_Return: J4.1, R5.2, R17.2
/AudioB2_In: J2.2, J10.3
/AudioB2_Return: J4.2, R6.2, R18.2
/AudioB3_In: J2.3, J10.5
/AudioB3_Return: J4.3, R7.2, R19.2
/AudioB4_In: J2.4, J10.7
/AudioB4_Return: J4.4, R8.2, R20.2
/Audio_Mix_A: J7.3, R11.1
/Audio_Mix_B: J8.3, R12.1
/Audio_Mix_Both: J9.3, R22.1
GND: C1.2, C2.2, J6.3, J6.4, J6.5, J6.6, J6.7, J6.8, J7.1, J8.1, J9.1, U1.3 (+), U1.5 (+), U1.10 (+), U1.12 (+)
unnamed: R10.1, R12.2, U1.7
unnamed: R9.1, R11.2, U1.1
unnamed: R21.1, R22.2, U1.8
unnamed: R1.1, R2.1, R3.1, R4.1, R9.2, U1.2 (-)
unnamed: R5.1, R6.1, R7.1, R8.1, R10.2, U1.6 (-)
unnamed: R13.1, R14.1, R15.1, R16.1, R17.1, R18.1, R19.1, R20.1, R21.2, U1.9 (-)
unnamed: U1.13 (-), U1.14

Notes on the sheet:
RJ45 Connectors
Power
Audio Mixed Output
Audio In
Mix Out
